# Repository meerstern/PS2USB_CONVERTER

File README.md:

# PS/2 USB逆変換アダプタ
Description of PS/2USB_CONVERTER. 

## 概要
PS/2 USB逆変換アダプタはUSBキーボードをPS/2化する変換アダプタです。

標準ドライバで動作可能なUSBキーボードをPS/2キーボードとして使用できるように変換します。

[世の中で販売されている変換アダプタ][0]とは変換の向きが逆です。

[市販USBキーボード]<-USB->[PS/2 USB逆変換アダプタ]<-PS/2->[PC,ichigojam]

プログラミング専用こどもパソコンichigojamやサーバマシンなどのPS/2キーボードのみをサポートしている場合にPS/2 USB逆変換アダプタを使用して、USBキーボードをPS/2化します。

## ichigojamで使用する場合
IchigoJam Tの場合はそのままキーボード用のUSB端子へPS/2 USB逆変換アダプタを接続してください。

IchigoJam Uと初代プリント基板の場合は同梱のUSB端子PS/2変換器を介して接続してください。

## 一般的なコンピュータで使用する場合
同梱のUSB端子PS/2変換器を介して接続してください。

## 注意
  * USBキーボードをPS/2規格に変換しているため、すべての機器やキー入力を保証することはできません。  
  * すべての機器で対応することを保証できません。  
  * 音量調整やメールボタンといったキーボード固有の機能は使用できません。
  * Logicool製日本語、英語キーボードで動作確認しましたが、すべてのUSBキーボードの動作保証はできません。
  * 日本語、英語以外の言語のキーボードでは入力できないキーがある場合があります。
  * PS/2規格に変換しているため、キーレスポンスやキーリピート等の挙動がUSBで接続する場合と多少異なります。
  * PS/2キーボードとPS/2マウス兼用ポートに接続した場合、不具合が発生する場合はあります。変換ケーブル等でキーボードとマウスを分離して接続してください。
  * USBハブを介した接続には対応していません。直接キーボードのUSBを接続してください。
  * キーレスポンスが遅延する場合は電源投入時リセットに失敗している可能性があります。キーボードのUSBを接続した状態で再度、当該アダプタを抜き差ししてください。  
  * USBマウスとPS/2との変換に非公式で対応しています（コンポジットデバイスでなく、マウスデバイス単体として認識されるマウスのみ対応）    

## 告知
  * 使用ICの価格高騰、入手性を考慮し、STM32+VNC2-32ベースからPIC32ベースに移行済(22年3月)
  * 移行前の製品と移行後の製品で基本機能は同じですが、キーレスポンス等異なる場合があります  ご了承ください 
  * 上記写真は移行前につき、移行後の製品は若干基板実装部品等異なります  
  * 同梱のPS/2変換器の色や形状、LED色等の仕様を告知なしに変更する場合があります  
  
 ## 販売サイト
  * [スイッチサイエンス][1]
  * [家電のケンちゃん][2]
  * [PCN][3]
  
[0]: http://www.aitendo.com/product/16414 "*0"
[1]: https://www.switch-science.com/products/3785
[2]: https://www.kadenken.com/view/item/000000000767
[3]: https://hello002.stores.jp/items/5bce8ce05f78661b790000ce

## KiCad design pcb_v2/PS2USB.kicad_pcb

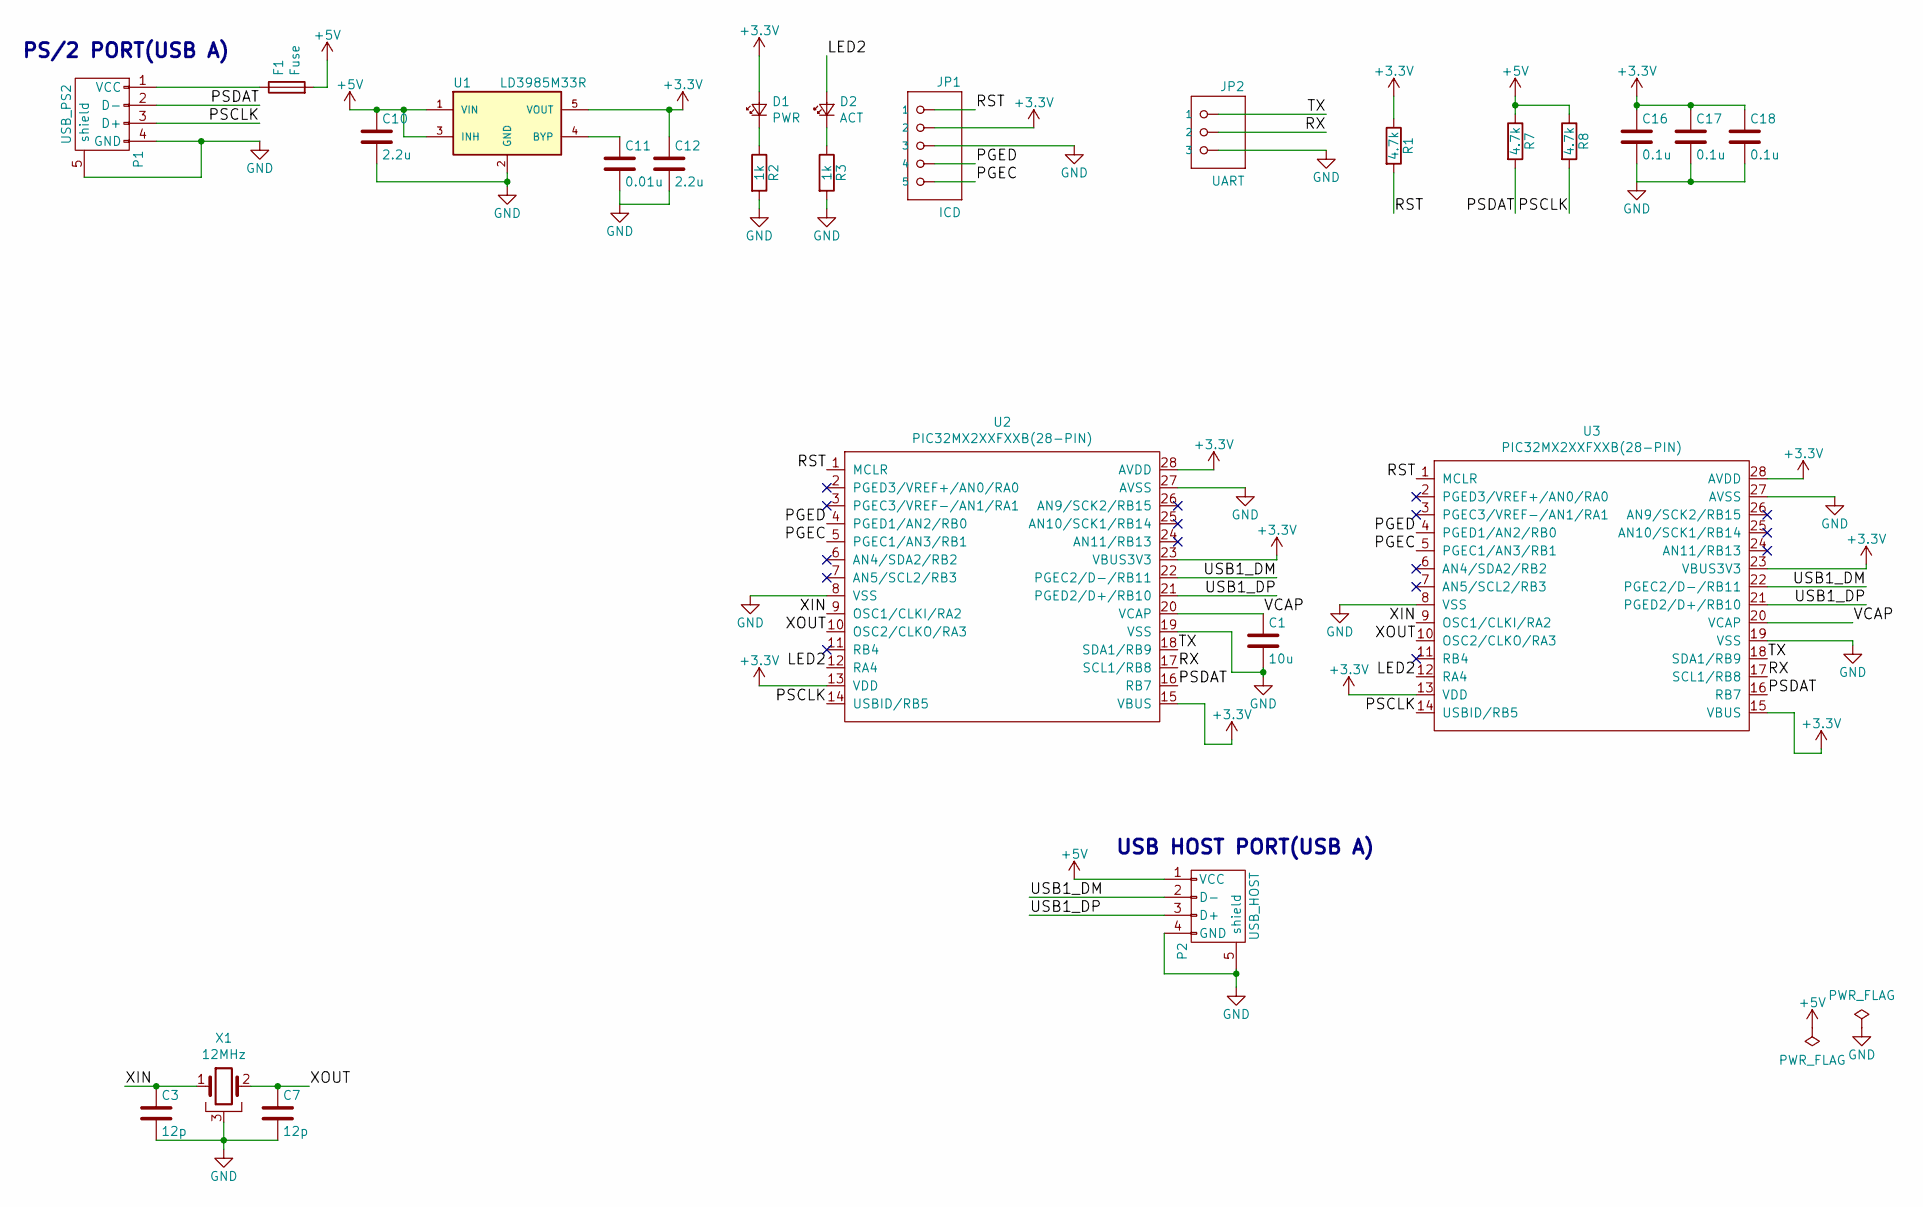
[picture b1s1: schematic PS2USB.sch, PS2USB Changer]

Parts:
C1: 10u; C_0805_2012Metric
C3, C7: 12p; C_0603_1608Metric
C10, C12: 2.2u; C_0603_1608Metric
C11: 0.01u; C_0603_1608Metric
C16, C17, C18: 0.1u; C_0603_1608Metric
D1: PWR; LED_0603_1608Metric
D2: ACT; LED_0603_1608Metric
F1: Fuse; Fuse_0603_1608Metric
JP1: ICD; PinHeader_1x05_P2.54mm_Vertical
JP2: UART; PinHeader_1x03_P2.54mm_Vertical
P1: USB_PS2; USBA
P2: USB_HOST; USBHOST
R1, R7, R8: 4.7k; R_0603_1608Metric
R2, R3: 1k; R_0603_1608Metric
U1: LD3985M33R; SOT-23-5
U2: PIC32MX2XXFXXB(28-PIN); SSOP-28_5.3x10.2mm_P0.65mm
U3: PIC32MX2XXFXXB(28-PIN); SOIC-28W_7.5x17.9mm_P1.27mm
X1: 12MHz; FA238V

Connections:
+3V3: C12.1, C16.1, C17.1, C18.1, D1.2 (A), JP1.2, R1.1, U1.5 (VOUT), U2.13 (VDD), U2.15 (VBUS), U2.23 (VBUS3V3), U2.28 (AVDD), U3.13 (VDD), U3.15 (VBUS), U3.23 (VBUS3V3), U3.28 (AVDD)
+5V: C10.1, F1.2, P2.1 (VCC), R7.1, R8.1, U1.1 (VIN), U1.3 (INH)
/LED2: D2.2 (A), U2.12 (RA4), U3.12 (RA4)
/PGEC: JP1.5, U2.5 (PGEC1/AN3/RB1), U3.5 (PGEC1/AN3/RB1)
/PGED: JP1.4, U2.4 (PGED1/AN2/RB0), U3.4 (PGED1/AN2/RB0)
/PSCLK: P1.3 (D+), R8.2, U2.14 (USBID/RB5), U3.14 (USBID/RB5)
/PSDAT: P1.2 (D-), R7.2, U2.16 (RB7), U3.16 (RB7)
/RST: JP1.1, R1.2, U2.1 (MCLR), U3.1 (MCLR)
/RX: JP2.2, U2.17 (SCL1/RB8), U3.17 (SCL1/RB8)
/TX: JP2.1, U2.18 (SDA1/RB9), U3.18 (SDA1/RB9)
/USB1_DM: P2.2 (D-), U2.22 (PGEC2/D-/RB11), U3.22 (PGEC2/D-/RB11)
/USB1_DP: P2.3 (D+), U2.21 (PGED2/D+/RB10), U3.21 (PGED2/D+/RB10)
/VCAP: C1.1, U2.20 (VCAP), U3.20 (VCAP)
/XIN: C3.1, U2.9 (OSC1/CLKI/RA2), U3.9 (OSC1/CLKI/RA2), X1.1
/XOUT: C7.1, U2.10 (OSC2/CLKO/RA3), U3.10 (OSC2/CLKO/RA3), X1.2
GND: C1.2, C3.2, C7.2, C10.2, C11.2, C12.2, C16.2, C17.2, C18.2, JP1.3, JP2.3, P1.4 (GND), P1.5 (shield), P2.4 (GND), P2.5 (shield), R2.2, R3.2, U1.2 (GND), U2.8 (VSS), U2.19 (VSS), U2.27 (AVSS), U3.8 (VSS), U3.19 (VSS), U3.27 (AVSS), X1.3
unnamed: C11.1, U1.4 (BYP)
unnamed: D1.1 (K), R2.1
unnamed: D2.1 (K), R3.1
unnamed: F1.1, P1.1 (VCC)

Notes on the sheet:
PS/2 PORT(USB A)
USB HOST PORT(USB A)

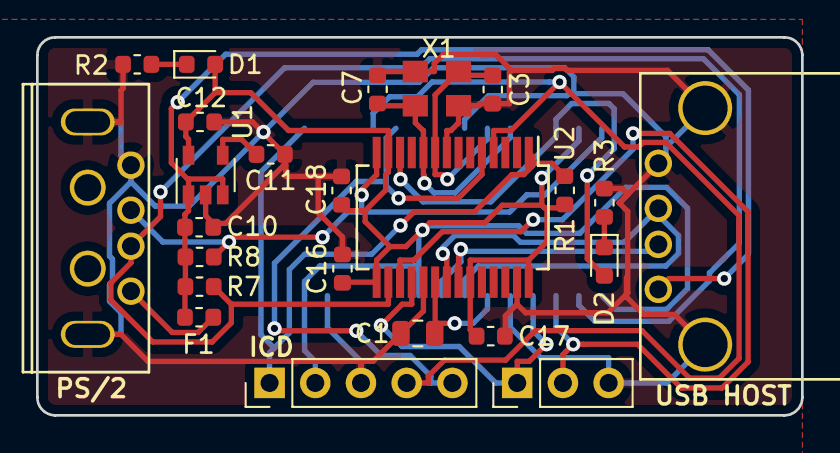
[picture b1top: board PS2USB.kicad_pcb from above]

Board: 2 copper layers, 42.5 x 21.0 mm, 25 parts (1 on the bottom side), 20 nets.

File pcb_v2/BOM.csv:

Elecrow PN,Parts,Value,Package,QTY,Digikey/Mouser/Manufacturer Part,Remark/ Link
4040806A,"D1,D2",LED,LED_0603_1608Metric,2,,
,U1,LD3985M33R,SOT-23-5,1,511-LD3985M33R,
C23162,"R1,R7,R8",4.7k,R_0603_1608Metric,3,,
C15850,C1,10u,C_0805_2012Metric,1,,
,P1,USB_PS2,USBA,1,490-UP2-AH-1-TH,
,F1,Fuse,Fuse_0603_1608Metric,1,650-FEMTOSMDC035F-02,
C14663,"C18,C17,C16",0.1u,C_0603_1608Metric,3,,
2014022A,"C12,C10",2.2u,C_0603_1608Metric,2,,
C57112,C11,0.01u,C_0603_1608Metric,1,,
C1644,"C7,C3",10p,C_0603_1608Metric,2,,
,P2,USB_HOST,USBHOST,1,530-SS-52100-001,
C21190,"R2,R3",1k,R_0603_1608Metric,2,,
,X1,12MHz,FA238V,1,ECS-120-12-33-AGN-TR3,
,U2,PIC32MX2XXFXXB(28-PIN),SSOP-28_5.3x10.2mm_P0.65mm,1,579-MX230F256B50I/SS,

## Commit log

2018-03-18 Init
2022-03-24 Add files
